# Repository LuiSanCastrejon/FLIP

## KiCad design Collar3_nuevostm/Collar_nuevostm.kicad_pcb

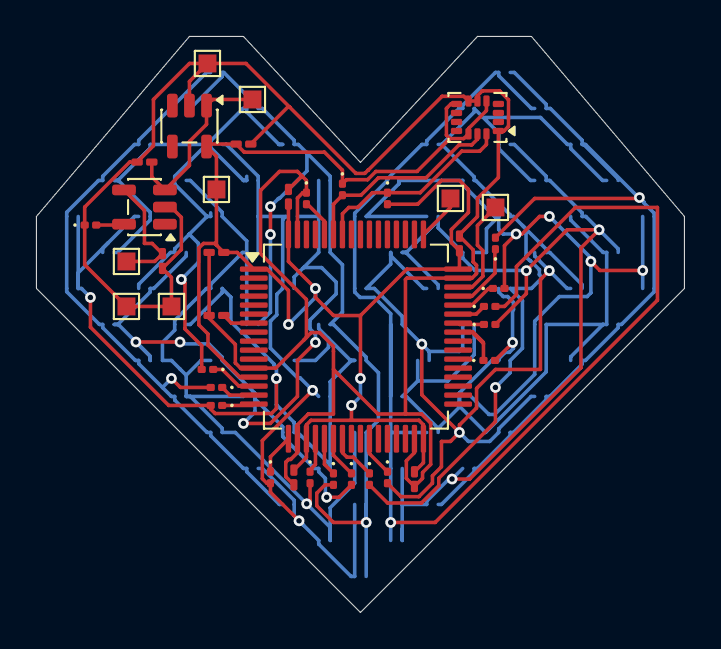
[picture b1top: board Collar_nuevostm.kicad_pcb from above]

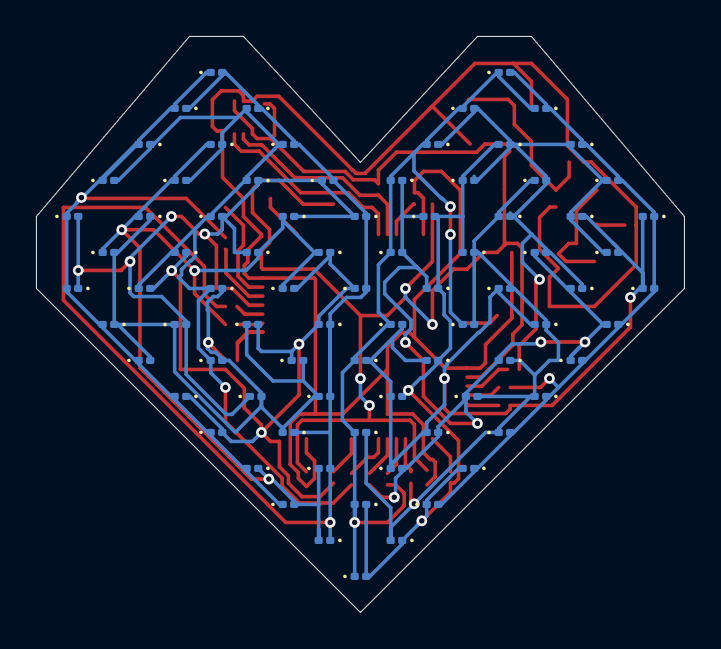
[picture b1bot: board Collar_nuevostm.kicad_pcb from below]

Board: 2 copper layers, 36.0 x 32.0 mm, 121 parts (82 on the bottom side), 39 nets.

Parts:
C1: C; C_0201_0603Metric_Pad0.64x0.40mm_HandSolder
C2, C3, C4, C5, C6, C7, C9: 100n; C_0201_0603Metric_Pad0.64x0.40mm_HandSolder
C8: 1n; C_0201_0603Metric_Pad0.64x0.40mm_HandSolder
D1, D2, D3, D4, D5, D6, D7, D8, D9, D10, D11, D12, D13, D14, D15, D16, D17, D18, D19, D20, D21, D22, D23, D24, D25, D26, D27, D28, D29, D30, D31, D32, D33, D34, D35, D36, D37, D38, D39, D40, D41, D42, D43, D44, D45, D46, D47, D48, D49, D50, D51, D52, D53, D54, D55, D56, D57, D58, D59, D60, D61, D62, D63, D64, D65, D66, D67, D68, D69, D70, D71, D72, D73, D74, D75, D76, D77, D78, D79, D80, D81, D82: LED; D_0201_0603Metric
GND1: TestPoint; TestPoint_Pad_1.0x1.0mm
GND2, GND3: VBAT1; TestPoint_Pad_1.0x1.0mm
R1, R2, R3, R4, R5, R6, R7, R14, R15, R16, R17, R18, R19, R20: 220; LED_0201_0603Metric
R8: 8k; LED_0201_0603Metric
R9, R10: 2.2k; LED_0201_0603Metric
R11: 10k; LED_0201_0603Metric
SWCLOCK1: TestPoint; TestPoint_Pad_1.0x1.0mm
SWDIO1: TestPoint; TestPoint_Pad_1.0x1.0mm
U2: LSM6DS3; LGA-14_3x2.5mm_P0.5mm_LayoutBorder3x4y
U3: AP2112K-3.3; SOT-23-5
U4: MCP73831-2-MC; SOT-23-5
U5: STM32L431RCTx; LQFP-64_10x10mm_P0.5mm
VBAT1: VBAT1; TestPoint_Pad_1.0x1.0mm
VCAR1: VBAT1; TestPoint_Pad_1.0x1.0mm
VCC1: TestPoint; TestPoint_Pad_1.0x1.0mm

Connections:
GND: C1.1, C2.1, C3.1, C4.1, C5.1, C6.1, C7.1, C8.1, C9.1, GND1.1 (1_1), GND2.1 (1_1), GND3.1 (1_1), R8.1, R11.1, U2.1 (SDO/SA0), U2.6 (GND), U2.7 (GND), U3.2 (GND), U4.2 (V_{SS}), U5.12 (VSSA), U5.18 (VSS), U5.31 (VSS), U5.47 (VSS), U5.63 (VSS)
unnamed: C1.2, U4.4 (V_{DD}), VCAR1.1 (1_1)
unnamed: D1.2 (A), D2.1 (K), D3.1 (K), D4.2 (A), D23.1 (K), D24.2 (A), D25.1 (K), D26.2 (A), D27.1 (K), D28.2 (A), D29.1 (K), D30.2 (A), R2.2
unnamed: D1.1 (K), D2.2 (A), D13.1 (K), D14.2 (A), D15.1 (K), D16.2 (A), D17.1 (K), D18.2 (A), D19.1 (K), D20.2 (A), D21.1 (K), D22.2 (A), R1.2
unnamed: D7.2 (A), D8.1 (K), D9.1 (K), D10.2 (A), D17.2 (A), D18.1 (K), D25.2 (A), D26.1 (K), D31.2 (A), D32.1 (K), D41.1 (K), D42.2 (A), R5.2
unnamed: D9.2 (A), D10.1 (K), D11.1 (K), D12.2 (A), D19.2 (A), D20.1 (K), D27.2 (A), D28.1 (K), D33.2 (A), D34.1 (K), D37.2 (A), D38.1 (K), R6.2
unnamed: D11.2 (A), D12.1 (K), D21.2 (A), D22.1 (K), D29.2 (A), D30.1 (K), D35.2 (A), D36.1 (K), D39.2 (A), D40.1 (K), D41.2 (A), D42.1 (K), R7.2
unnamed: D3.2 (A), D4.1 (K), D5.1 (K), D6.2 (A), D13.2 (A), D14.1 (K), D31.1 (K), D32.2 (A), D33.1 (K), D34.2 (A), D35.1 (K), D36.2 (A), R3.2
unnamed: D5.2 (A), D6.1 (K), D7.1 (K), D8.2 (A), D15.2 (A), D16.1 (K), D23.2 (A), D24.1 (K), D37.1 (K), D38.2 (A), D39.1 (K), D40.2 (A), R4.2
unnamed: D43.2 (A), D44.1 (K), D45.1 (K), D46.2 (A), D65.1 (K), D66.2 (A), D67.1 (K), D68.2 (A), D69.1 (K), D70.2 (A), D71.1 (K), D72.2 (A), R15.2
unnamed: D43.1 (K), D44.2 (A), D47.1 (K), D49.2 (A), D51.1 (K), D53.2 (A), D55.1 (K), D57.2 (A), D59.1 (K), D61.2 (A), D63.1 (K), D64.2 (A), R14.2
unnamed: D45.2 (A), D46.1 (K), D47.2 (A), D48.1 (K), D49.1 (K), D50.2 (A), D73.1 (K), D74.2 (A), D75.1 (K), D76.2 (A), D77.1 (K), D78.2 (A), R16.2
unnamed: D48.2 (A), D50.1 (K), D51.2 (A), D52.1 (K), D53.1 (K), D54.2 (A), D65.2 (A), D66.1 (K), D79.1 (K), D80.2 (A), D81.1 (K), D82.2 (A), R17.2
unnamed: D52.2 (A), D54.1 (K), D55.2 (A), D56.1 (K), D57.1 (K), D58.2 (A), D67.2 (A), D68.1 (K), D73.2 (A), D74.1 (K), R18.2
unnamed: D56.2 (A), D58.1 (K), D59.2 (A), D60.1 (K), D61.1 (K), D62.2 (A), D69.2 (A), D70.1 (K), D75.2 (A), D76.1 (K), D79.2 (A), D80.1 (K), R19.2
unnamed: D60.2 (A), D62.1 (K), D63.2 (A), D64.1 (K), D71.2 (A), D72.1 (K), D77.2 (A), D78.1 (K), D81.2 (A), D82.1 (K), R20.2
unnamed: C2.2, C4.2, C5.2, C6.2, C7.2, C9.2, R9.1, R10.2, U2.5 (VDDIO), U2.8 (VDD), U2.12 (CS), U3.5 (VOUT), U5.1 (VBAT), U5.13 (VDDA), U5.19 (VDD), U5.32 (VDD), U5.48 (VDD), U5.64 (VDD), VCC1.1 (1_1)
unnamed: R9.2, U2.13 (SCL), U5.59 (PB7)
unnamed: R10.1, U2.14 (SDA), U5.58 (PB6)
unnamed: C8.2, U3.1 (VIN), U4.3 (V_{BAT}), VBAT1.1 (1_1)
unnamed: R8.2, U4.5 (PROG)
unnamed: C3.2, U5.7 (NRST)
unnamed: R1.1, U5.14 (PA0)
unnamed: R2.1, U5.15 (PA1)
unnamed: R3.1, U5.16 (PA2)
unnamed: R4.1, U5.17 (PA3)
unnamed: R5.1, U5.20 (PA4)
unnamed: R6.1, U5.21 (PA5)
unnamed: R7.1, U5.22 (PA6)
unnamed: R14.1, U5.23 (PA7)
unnamed: R15.1, U5.41 (PA8)
unnamed: R16.1, U5.42 (PA9)
unnamed: R17.1, U5.43 (PA10)
unnamed: R18.1, U5.44 (PA11)
unnamed: R19.1, U5.45 (PA12)
unnamed: SWDIO1.1 (1_1), U5.46 (PA13)
unnamed: SWCLOCK1.1 (1_1), U5.49 (PA14)
unnamed: R20.1, U5.26 (PB0)
unnamed: R11.2, U5.60 (PH3)
